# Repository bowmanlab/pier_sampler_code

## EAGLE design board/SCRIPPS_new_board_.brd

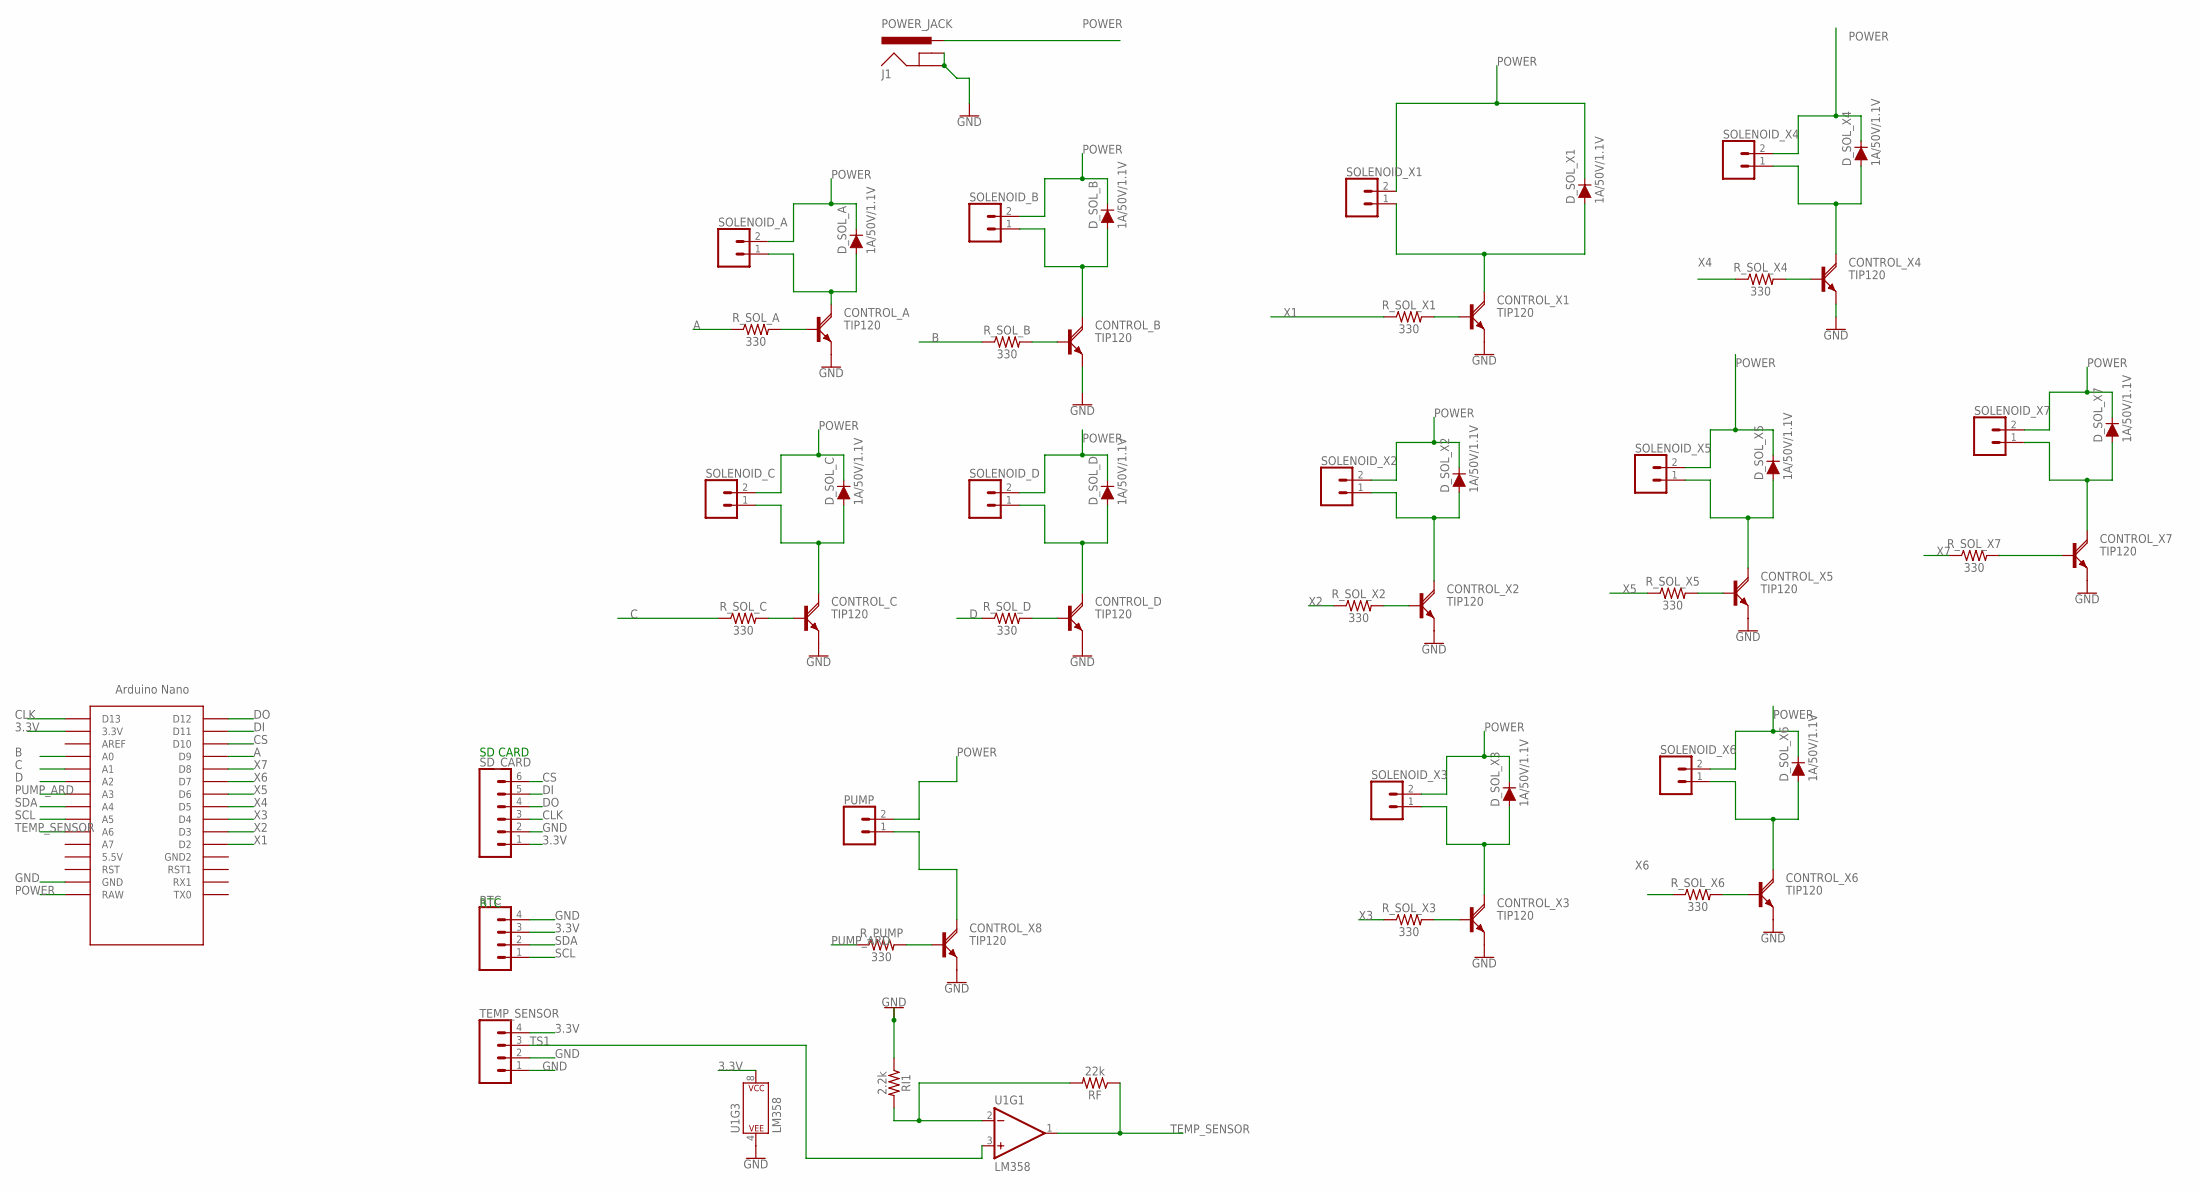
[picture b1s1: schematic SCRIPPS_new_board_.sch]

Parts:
CONTROL_A: TIP120; TO220AH
CONTROL_B: TIP120; TO220AH
CONTROL_C: TIP120; TO220AH
CONTROL_D: TIP120; TO220AH
CONTROL_X1, CONTROL_X2, CONTROL_X3, CONTROL_X4, CONTROL_X5, CONTROL_X6, CONTROL_X7, CONTROL_X8: TIP120; TO220AH
D_SOL_A: 1A/50V/1.1V; DIODE-1N4001
D_SOL_B: 1A/50V/1.1V; DIODE-1N4001
D_SOL_C: 1A/50V/1.1V; DIODE-1N4001
D_SOL_D: 1A/50V/1.1V; DIODE-1N4001
D_SOL_X1, D_SOL_X2, D_SOL_X3, D_SOL_X4, D_SOL_X5, D_SOL_X6, D_SOL_X7: 1A/50V/1.1V; DIODE-1N4001
J1: POWER_JACK; POWER_JACK_PTH
PUMP: CONN_02; 1X02
RF: 22k; AXIAL-0.3
RI1: 2.2k; AXIAL-0.3
RTC: CONN_04; 1X04
R_PUMP: 330; AXIAL-0.3
R_SOL_A: 330; AXIAL-0.3
R_SOL_B: 330; AXIAL-0.3
R_SOL_C: 330; AXIAL-0.3
R_SOL_D: 330; AXIAL-0.3
R_SOL_X1, R_SOL_X2, R_SOL_X3, R_SOL_X4, R_SOL_X5, R_SOL_X6, R_SOL_X7: 330; AXIAL-0.3
SD_CARD: CONN_06FEMALE_LOCK; 1X06_FEMALE_LOCK.010
SOLENOID_A: CONN_02; 1X02
SOLENOID_B: CONN_02; 1X02
SOLENOID_C: CONN_02; 1X02
SOLENOID_D: CONN_02; 1X02
SOLENOID_X1, SOLENOID_X2, SOLENOID_X3, SOLENOID_X4, SOLENOID_X5, SOLENOID_X6, SOLENOID_X7: CONN_02; 1X02
TEMP_SENSOR: CONN_04; 1X04
U1: LM358; DIP08
U$2: NANO

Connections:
3.3V: RTC.3, SD_CARD.1, TEMP_SENSOR.4, U1.8 (P$V+), U$2.3.3V
A: R_SOL_A.P$1 (1), U$2.D9
B: R_SOL_B.P$1 (1), U$2.A0
C: R_SOL_C.P$1 (1), U$2.A1
CLK: SD_CARD.3, U$2.D13
CS: SD_CARD.6, U$2.D10
D: R_SOL_D.P$1 (1), U$2.A2
DI: SD_CARD.5, U$2.D11
DO: SD_CARD.4, U$2.D12
unnamed: CONTROL_X8.B, R_PUMP.P$2 (2)
unnamed: CONTROL_X8.C, PUMP.1
unnamed: CONTROL_X1.C, D_SOL_X1.A, SOLENOID_X1.1
unnamed: CONTROL_X1.B, R_SOL_X1.P$2 (2)
unnamed: CONTROL_C.B, R_SOL_C.P$2 (2)
unnamed: CONTROL_A.B, R_SOL_A.P$2 (2)
unnamed: CONTROL_A.C, D_SOL_A.A, SOLENOID_A.1
unnamed: CONTROL_C.C, D_SOL_C.A, SOLENOID_C.1
unnamed: RF.P$2 (2), RI1.P$2 (2), U1.2 (-IN)
unnamed: CONTROL_B.B, R_SOL_B.P$2 (2)
unnamed: CONTROL_B.C, D_SOL_B.A, SOLENOID_B.1
unnamed: CONTROL_D.B, R_SOL_D.P$2 (2)
unnamed: CONTROL_D.C, D_SOL_D.A, SOLENOID_D.1
unnamed: CONTROL_X5.B, R_SOL_X5.P$2 (2)
unnamed: CONTROL_X2.C, D_SOL_X2.A, SOLENOID_X2.1
unnamed: CONTROL_X7.B, R_SOL_X7.P$2 (2)
unnamed: CONTROL_X7.C, D_SOL_X7.A, SOLENOID_X7.1
unnamed: CONTROL_X5.C, D_SOL_X5.A, SOLENOID_X5.1
unnamed: CONTROL_X4.B, R_SOL_X4.P$2 (2)
unnamed: CONTROL_X4.C, D_SOL_X4.A, SOLENOID_X4.1
unnamed: CONTROL_X2.B, R_SOL_X2.P$2 (2)
unnamed: CONTROL_X3.B, R_SOL_X3.P$2 (2)
unnamed: CONTROL_X3.C, D_SOL_X3.A, SOLENOID_X3.1
unnamed: CONTROL_X6.B, R_SOL_X6.P$2 (2)
unnamed: CONTROL_X6.C, D_SOL_X6.A, SOLENOID_X6.1
POWER: D_SOL_A.C, D_SOL_B.C, D_SOL_C.C, D_SOL_D.C, D_SOL_X1.C, D_SOL_X2.C, D_SOL_X3.C, D_SOL_X4.C, D_SOL_X5.C, D_SOL_X6.C, D_SOL_X7.C, J1.PWR, PUMP.2, SOLENOID_A.2, SOLENOID_B.2, SOLENOID_C.2, SOLENOID_D.2, SOLENOID_X1.2, SOLENOID_X2.2, SOLENOID_X3.2, SOLENOID_X4.2, SOLENOID_X5.2, SOLENOID_X6.2, SOLENOID_X7.2, U$2.RAW
PUMP_ARD: R_PUMP.P$1 (1), U$2.A3
SCL: RTC.1, U$2.A5
SDA: RTC.2, U$2.A4
TEMP_SENSOR: RF.P$1 (1), U1.1 (OUT), U$2.A6
TS1: TEMP_SENSOR.3, U1.3 (+IN)
X1: R_SOL_X1.P$1 (1), U$2.D2
X2: R_SOL_X2.P$1 (1), U$2.D3
X3: R_SOL_X3.P$1 (1), U$2.D4
X4: R_SOL_X4.P$1 (1), U$2.D5
X5: R_SOL_X5.P$1 (1), U$2.D6
X6: R_SOL_X6.P$1 (1), U$2.D7
X7: R_SOL_X7.P$1 (1), U$2.D8

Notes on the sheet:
SD CARD
RTC

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
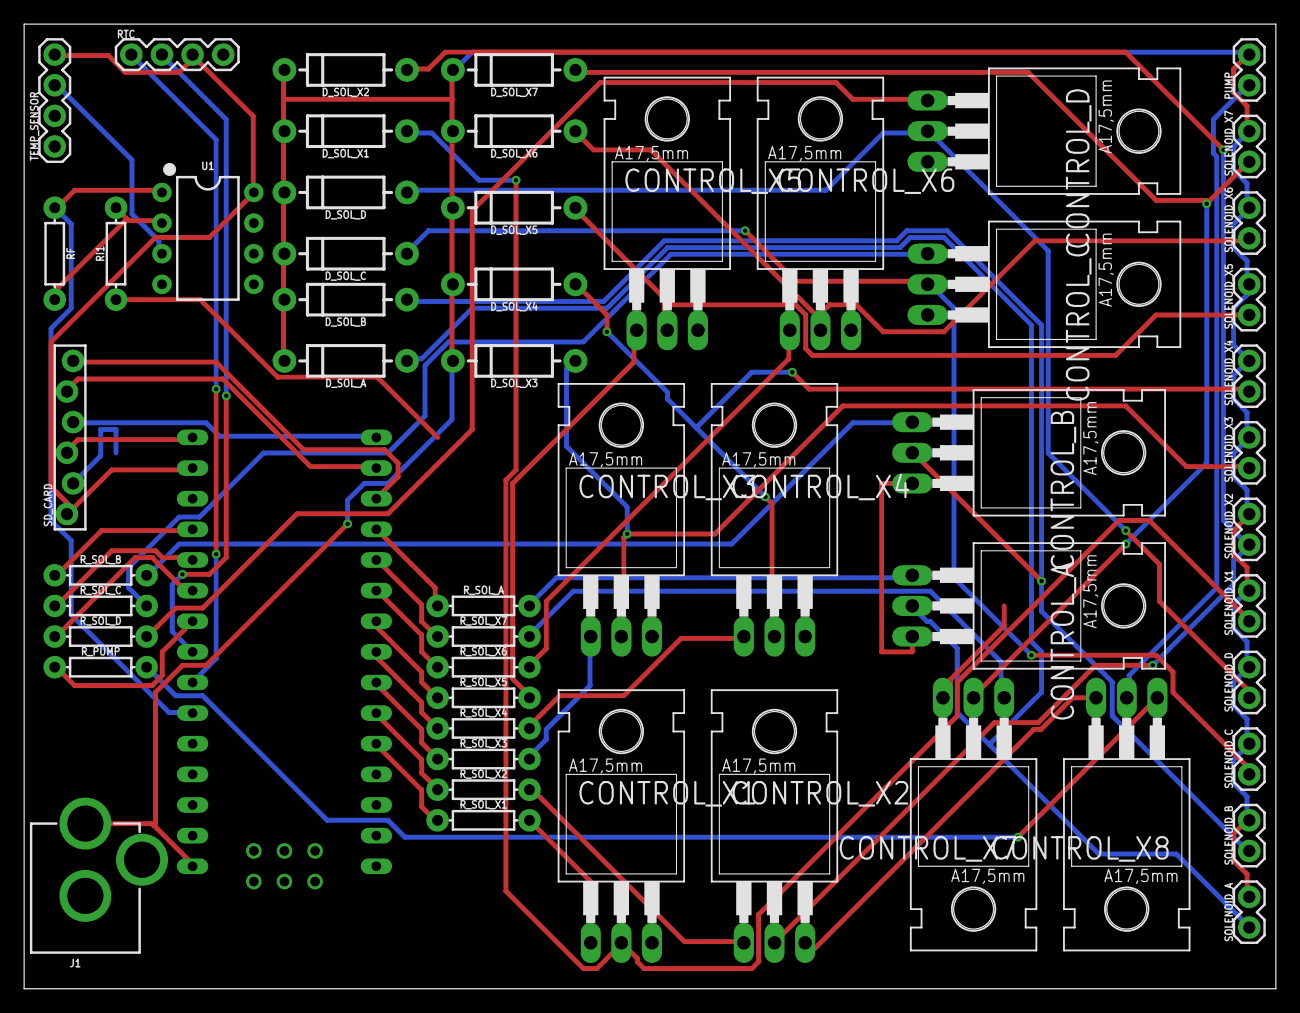
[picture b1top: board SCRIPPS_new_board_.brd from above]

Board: 2 copper layers, 103.8 x 80.0 mm, 55 parts (0 on the bottom side), 48 nets.

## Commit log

2017-02-02 :neckbeard: Added .gitattributes
2017-02-14 Code_draft_1
    Initial draft
2017-02-14 added author header
2017-03-07 complete_code_V1
2017-04-17 Code with updated comments
2017-04-24 Update_2
2017-04-24 Update_with_comments
2017-06-12 add CAD files
2018-01-30 new board and code
2018-04-05 add Ari's (excellent) documentation

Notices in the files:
parts and their libraries:
SparkFun-DiscreteSemi: Licensing: Creative Commons ShareAlike 4.0 International - https://creativecommons.org/licenses/by-sa/4.0
